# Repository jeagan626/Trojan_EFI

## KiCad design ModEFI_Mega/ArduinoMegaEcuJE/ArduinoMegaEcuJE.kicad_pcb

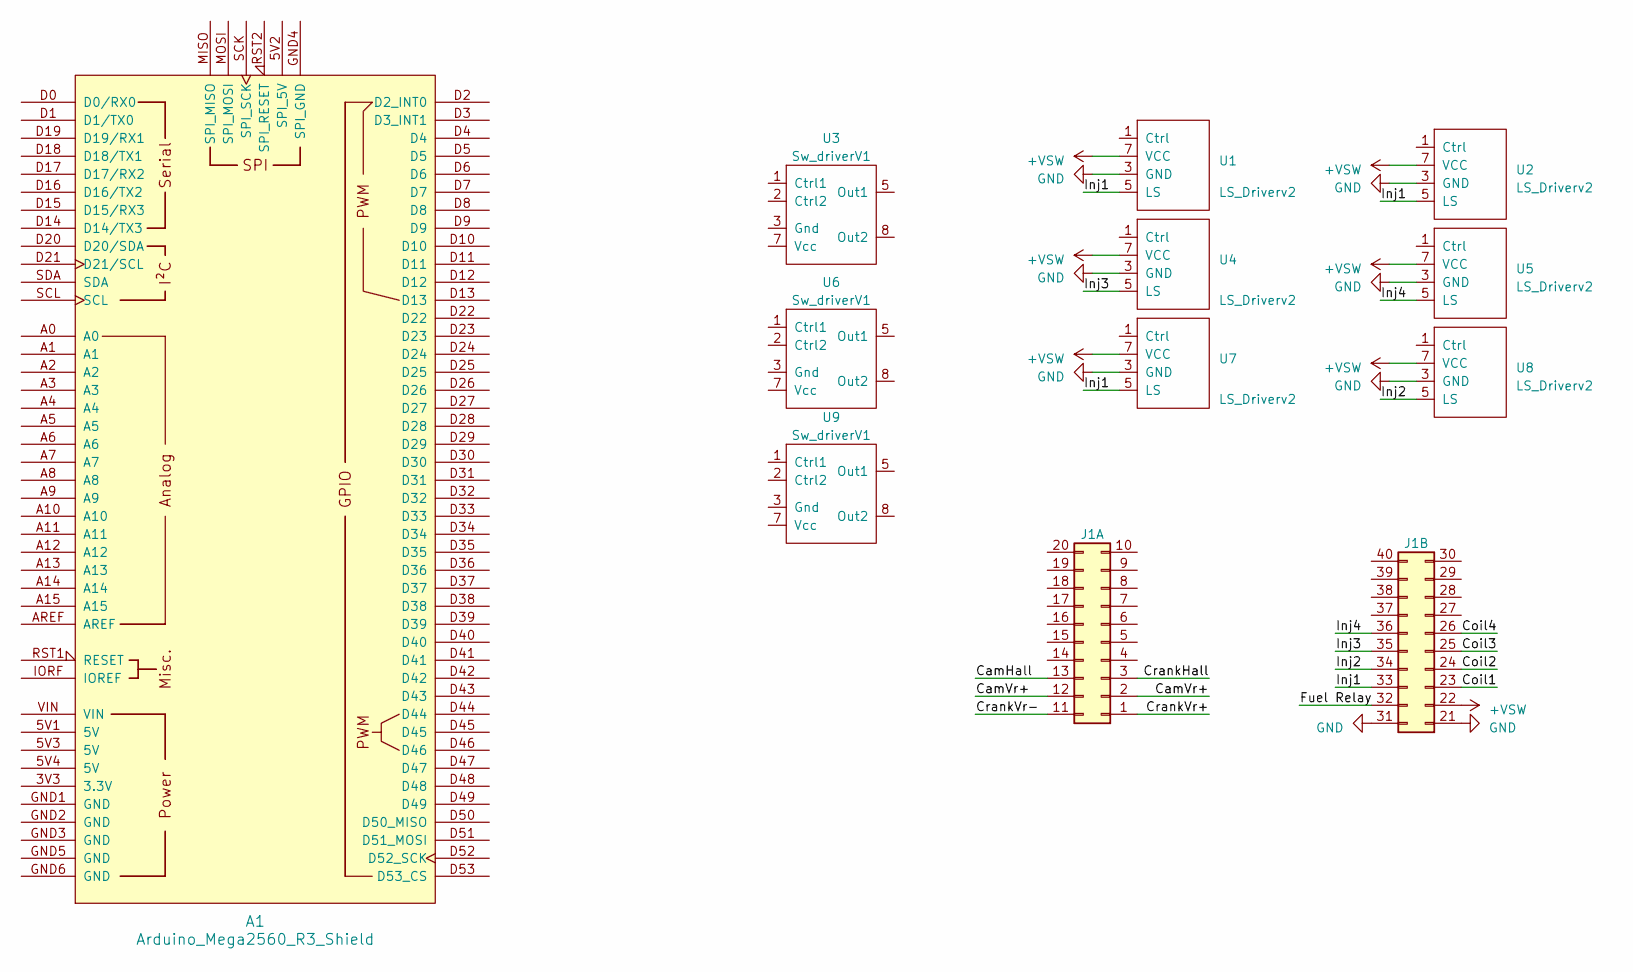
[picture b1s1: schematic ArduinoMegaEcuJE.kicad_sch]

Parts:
A1: Arduino_Mega2560_R3_Shield
J1: MQS40P
U1, U2, U4, U5, U7, U8: LS_Driverv2; DIP-8_W7.62mm_Socket_LongPads
U3, U6, U9: Sw_driverV1

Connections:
+VSW: J1.22, U1.7 (VCC), U2.7 (VCC), U4.7 (VCC), U5.7 (VCC), U7.7 (VCC), U8.7 (VCC)
/CamHall: J1.13
/CamVr+: J1.2, J1.12
/Coil1: J1.23
/Coil2: J1.24
/Coil3: J1.25
/Coil4: J1.26
/CrankHall: J1.3
/CrankVr+: J1.1
/CrankVr-: J1.11
/Fuel Relay: J1.32
/Inj1: J1.33, U1.5 (LS), U1.6 (LS), U2.5 (LS), U2.6 (LS), U7.5 (LS), U7.6 (LS)
/Inj2: J1.34, U8.5 (LS), U8.6 (LS)
/Inj3: J1.35, U4.5 (LS), U4.6 (LS)
/Inj4: J1.36, U5.5 (LS), U5.6 (LS)
GND: J1.21, J1.31, U1.3 (GND), U1.4 (GND), U2.3 (GND), U2.4 (GND), U4.3 (GND), U4.4 (GND), U5.3 (GND), U5.4 (GND), U7.3 (GND), U7.4 (GND), U8.3 (GND), U8.4 (GND)
unnamed: U3.3 (Gnd), U3.4 (Gnd)
unnamed: U3.5 (Out1), U3.6 (Out1)
unnamed: U6.3 (Gnd), U6.4 (Gnd)
unnamed: U6.5 (Out1), U6.6 (Out1)
unnamed: U9.3 (Gnd), U9.4 (Gnd)
unnamed: U9.5 (Out1), U9.6 (Out1)

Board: 2 copper layers, 11 parts (10 on the bottom side), 13 nets, no tracks yet.

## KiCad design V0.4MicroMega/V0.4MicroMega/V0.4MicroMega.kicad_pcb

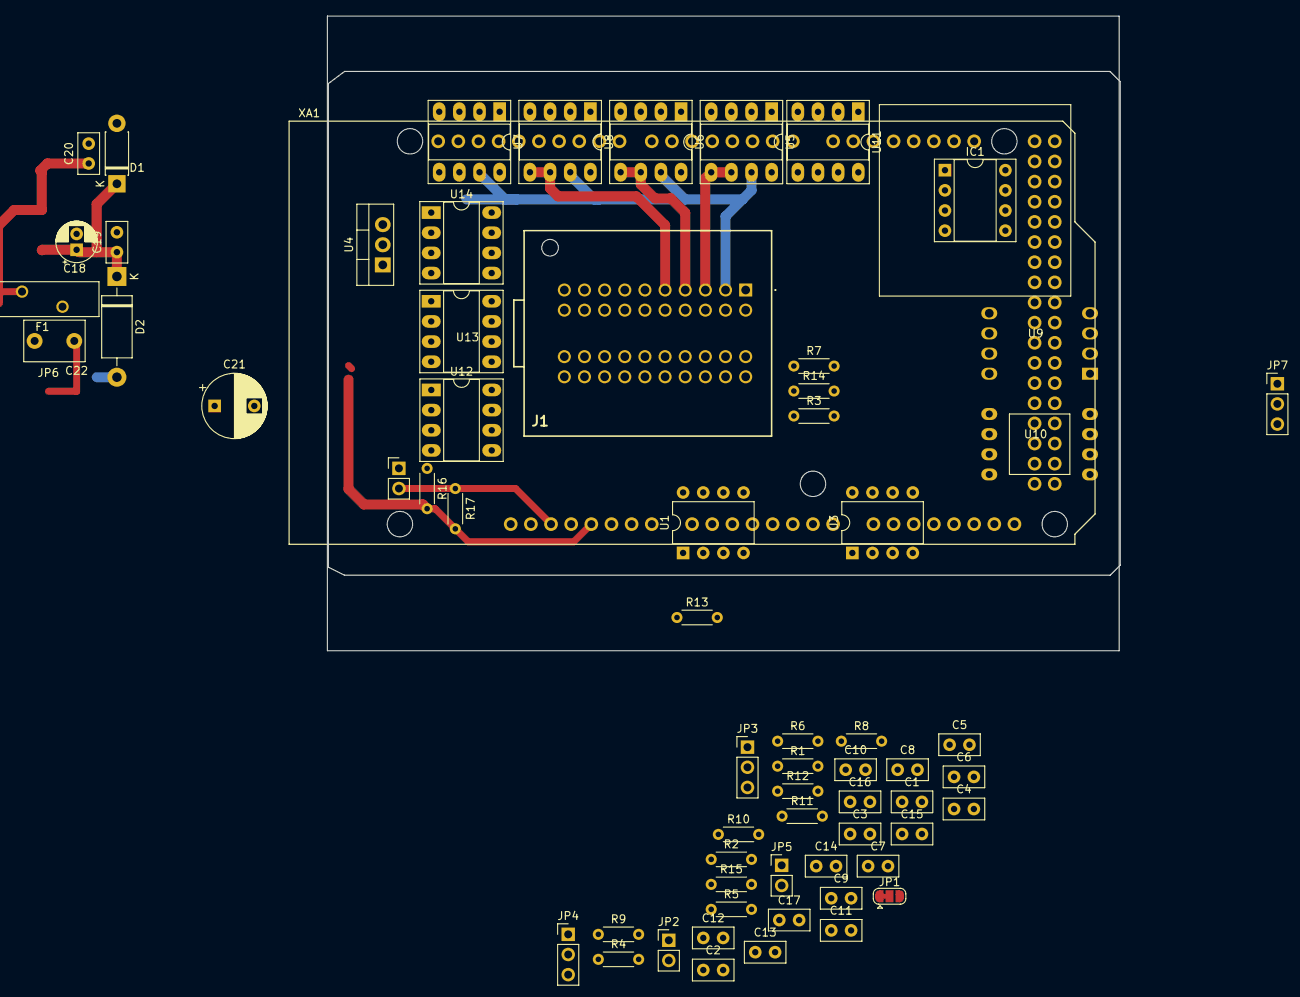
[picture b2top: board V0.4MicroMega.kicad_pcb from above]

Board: 2 copper layers, 99.8 x 80.0 mm, 65 parts (0 on the bottom side), 56 nets.

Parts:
C1, C11: 0.01uF; C_Disc_D5.0mm_W2.5mm_P2.50mm
C2: 1uF; C_Disc_D5.0mm_W2.5mm_P2.50mm
C3, C6: 470pf; C_Disc_D5.0mm_W2.5mm_P2.50mm
C4, C7, C9, C12, C13, C15, C19, C20: 0.1uF; C_Disc_D5.0mm_W2.5mm_P2.50mm
C5, C8, C10, C14, C16, C17: 0.22uF; C_Disc_D5.0mm_W2.5mm_P2.50mm
C18: 10uF; CP_Radial_D5.0mm_P2.00mm
C21: 47uF; CP_Radial_D8.0mm_P5.00mm
C22: 22uF; C_Disc_D7.5mm_W5.0mm_P5.00mm
D1: SB230TA; D_DO-41_SOD81_P7.62mm_Horizontal
D2: D_TVS; D_DO-15_P12.70mm_Horizontal
F1: Polyfuse; Fuse_BelFuse_0ZRE0055FF_L14.0mm_W4.1mm
IC1: Trig Cond Socket; DIP-8_W7.62mm_Socket
J1: 953118-1; 9531181
JP1: Jumper_3_Bridged12; SolderJumper-3_P1.3mm_Bridged12_RoundedPad1.0x1.5mm
JP2, JP5: PULL-UP; PinHeader_1x02_P2.54mm_Vertical
JP3, JP4: VR-HALL; PinHeader_1x03_P2.54mm_Vertical
JP6: Jumper_NO_Small; PinHeader_1x02_P2.54mm_Vertical
JP7: Ignition Voltage; PinHeader_1x03_P2.54mm_Vertical
R1, R2, R3, R5, R6, R10, R11: 470R; R_Axial_DIN0204_L3.6mm_D1.6mm_P5.08mm_Horizontal
R4, R8: 2.49k; R_Axial_DIN0204_L3.6mm_D1.6mm_P5.08mm_Horizontal
R7, R12, R13, R14: 1k; R_Axial_DIN0204_L3.6mm_D1.6mm_P5.08mm_Horizontal
R9: 3.9k; R_Axial_DIN0204_L3.6mm_D1.6mm_P5.08mm_Horizontal
R15: 2.4k; R_Axial_DIN0204_L3.6mm_D1.6mm_P5.08mm_Horizontal
R16: 120R; R_Axial_DIN0204_L3.6mm_D1.6mm_P5.08mm_Horizontal
R17: 10k; R_Axial_DIN0204_L3.6mm_D1.6mm_P5.08mm_Horizontal
U1, U3: SP721; DIP-8_W7.62mm
U4: LM2940S-5.0; TO-220-3_Vertical
U5, U6, U7, U8, U11, U12, U13, U14: LS_Driverv2; DIP-8_W7.62mm_Socket_LongPads
U9, U10: Sw_driverV1
XA1: Arduino_Mega2560_Shield

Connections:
12V-SW: D1.2 (A), J1.2, JP7.3 (B), R9.2, U5.7 (VCC), U6.7 (VCC), U7.7 (VCC), U8.7 (VCC), U11.7 (VCC), U12.7 (VCC), U13.7 (VCC), U14.7 (VCC)
ADC-Clamp-2: C3.2, R2.1, U1.2 (I2), XA1.A3
ADC-Clamp-3: C5.1, R1.1, U1.3 (I3), XA1.A2
ADC-Clamp-5: C8.1, R5.1, U1.6 (I5), XA1.A0
ADC-Clamp-6: C14.1, R10.1, U1.7 (I6), XA1.A1
ADC-Clamp-7: C17.1, J1.38, R15.2, U3.1 (I1), XA1.D2 (D2_INT0)
ADC-Clamp-8: C12.2, IC1.7, JP4.3 (B), U3.2 (I2), XA1.D18 (D18_TX1)
ADC-Clamp-9: C11.2, IC1.8, JP3.3 (B), U3.3 (I3), XA1.D19 (D19_RX1)
ADC-Clamp-10: R14.2, U3.5 (I4), XA1.D51
ADC-Clamp-11: C10.1, R6.1, U3.6 (I5), XA1.A8
ADC-Clamp-12: C16.1, R11.1, U3.7 (I6), XA1.A4
BOOST-OUT: J1.19, U12.5 (LS), U12.6 (LS)
CAM-IN: JP4.2 (C), JP5.1 (A)
CLT_Sensor: C13.1, J1.36, R8.1, R10.2
CRANK-IN: JP2.1 (A), JP3.2 (C)
FAN-OUT: J1.9, U13.5 (LS), U13.6 (LS)
FUELPUMP-OUT: J1.12, U11.5 (LS), U11.6 (LS)
GND: C1.1, C2.1, C3.1, C4.2, C5.2, C6.2, C7.2, C8.2, C9.2, C10.2, C11.1, C12.1, C13.2, C14.2, C15.2, C16.2, C17.2, C18.2, C19.2, C20.2, C21.2, C22.2, D2.2 (A), IC1.6, J1.1, J1.11, R12.1, U1.4 (GND), U3.4 (GND), U4.2 (GND), U5.3 (GND), U5.4 (GND), U6.3 (GND), U6.4 (GND), U7.3 (GND), U7.4 (GND), U8.3 (GND), U8.4 (GND), U9.3 (Gnd), U9.4 (Gnd), U10.3 (Gnd), U10.4 (Gnd), U11.3 (GND), U11.4 (GND), U12.3 (GND), U12.4 (GND), U13.3 (GND), U13.4 (GND), U14.3 (GND), U14.4 (GND), XA1.GND1 (GND), XA1.GND2 (GND), XA1.GND3 (GND), XA1.GND5 (GND), XA1.GND6 (GND)
IAT_Sensor: C7.1, J1.26, R4.1, R5.2
IDLE-OUT: J1.10, U14.5 (LS), U14.6 (LS)
IGN-1-OUT: J1.13, U9.8 (Out2)
IGN-2-OUT: J1.14, U9.5 (Out1), U9.6 (Out1)
IGN-3-OUT: J1.15, U10.8 (Out2)
IGN-4-OUT: J1.16, U10.5 (Out1), U10.6 (Out1)
INJ-1-OUT: J1.3, U5.5 (LS), U5.6 (LS)
INJ-2-OUT: J1.4, U6.5 (LS), U6.6 (LS)
INJ-3-OUT: J1.5, U8.5 (LS), U8.6 (LS)
INJ-4-OUT: J1.6, U7.5 (LS), U7.6 (LS)
MAP-EXT: J1.25, JP1.1 (A), R2.2
MCU-A5: C6.1, R3.1, XA1.A5
MCU-D5: U14.1 (Ctrl), XA1.D5
MCU-D7: U12.1 (Ctrl), XA1.D7
MCU-D8: U5.1 (Ctrl), XA1.D8
MCU-D9: U6.1 (Ctrl), XA1.D9
MCU-D10: U8.1 (Ctrl), XA1.D10
MCU-D11: U7.1 (Ctrl), XA1.D11
MCU-D38: U9.1 (Ctrl1), XA1.D38
MCU-D40: U9.2 (Ctrl2), XA1.D40
MCU-D45: U11.1 (Ctrl), XA1.D45
MCU-D47: U13.1 (Ctrl), XA1.D47
MCU-D50: U10.1 (Ctrl1), XA1.D50
MCU-D52: U10.2 (Ctrl2), XA1.D52
unnamed: C15.1, R9.1, R11.2, R12.2
unnamed: C22.1, JP6.1, R16.1
unnamed: IC1.2, JP3.1 (A)
unnamed: IC1.3, JP4.1 (A)
unnamed: JP1.3 (B), R3.2
unnamed: JP2.2 (B), R7.1
unnamed: JP5.2 (B), R13.1
O2_Sensor: C9.1, J1.28, R6.2
RESET: JP6.2, R17.1, XA1.RST1 (RESET)
TPS_Sensor: C4.1, J1.35, R1.2
VDD: C1.2, C2.2, C20.1, C21.1, F1.2, IC1.5, JP7.1 (A), R16.2, R17.2, U4.3 (VO), XA1.5V1 (5V), XA1.5V3 (5V), XA1.5V4 (5V)
VDDA: F1.1, J1.24, R4.2, R7.2, R8.2, R13.2, R15.1, U1.8 (V+), U3.8 (V+)
VRegIn: C18.1, C19.1, D1.1 (K), D2.1 (K), U4.1 (VI)
Vdrive: JP7.2 (C), U9.7 (Vcc), U10.7 (Vcc)

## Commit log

2021-07-19 Added SignalBufferBoard
2021-07-19 Updated Buffer Board Design
2021-08-03 Added New updated and boards
2021-08-08 Updated boards
2023-11-17 Started modEFI Speeduino
